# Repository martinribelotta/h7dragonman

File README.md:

# H7-DragonMAN board

STM32H7 LQFP100 board for protocol bridge and industrial control.

## Characterstics:

 - Isolated (see `isolated` branch) and non isolated version
 - STM32H750/743VxTx400MHz in 100LQFP with 8MHz/32.768Khz crystals and ROM Bootloader via USB
 - STM32-based DAP programmer and virtual usb with ROM bootloader via USB
 - External 2/4/8/16MB QSPI flash
 - MicroSD card 1bit slot
 - Two usb otg (FS and HS)
 - 10/100Mb ETH via KSZ8081 in RMII mode
 - RS485 isolated or non-isolated
 - CANBUS isolated or non-isolated
 - Isolated 3.3 to 5V step-up for CANBUS/RS-485 tranceivers
 - One user button
 - One user led
 - 5-24V input via AP63203 DC-DC regulator

## Schematic

## Board dimentions

## 3D preview

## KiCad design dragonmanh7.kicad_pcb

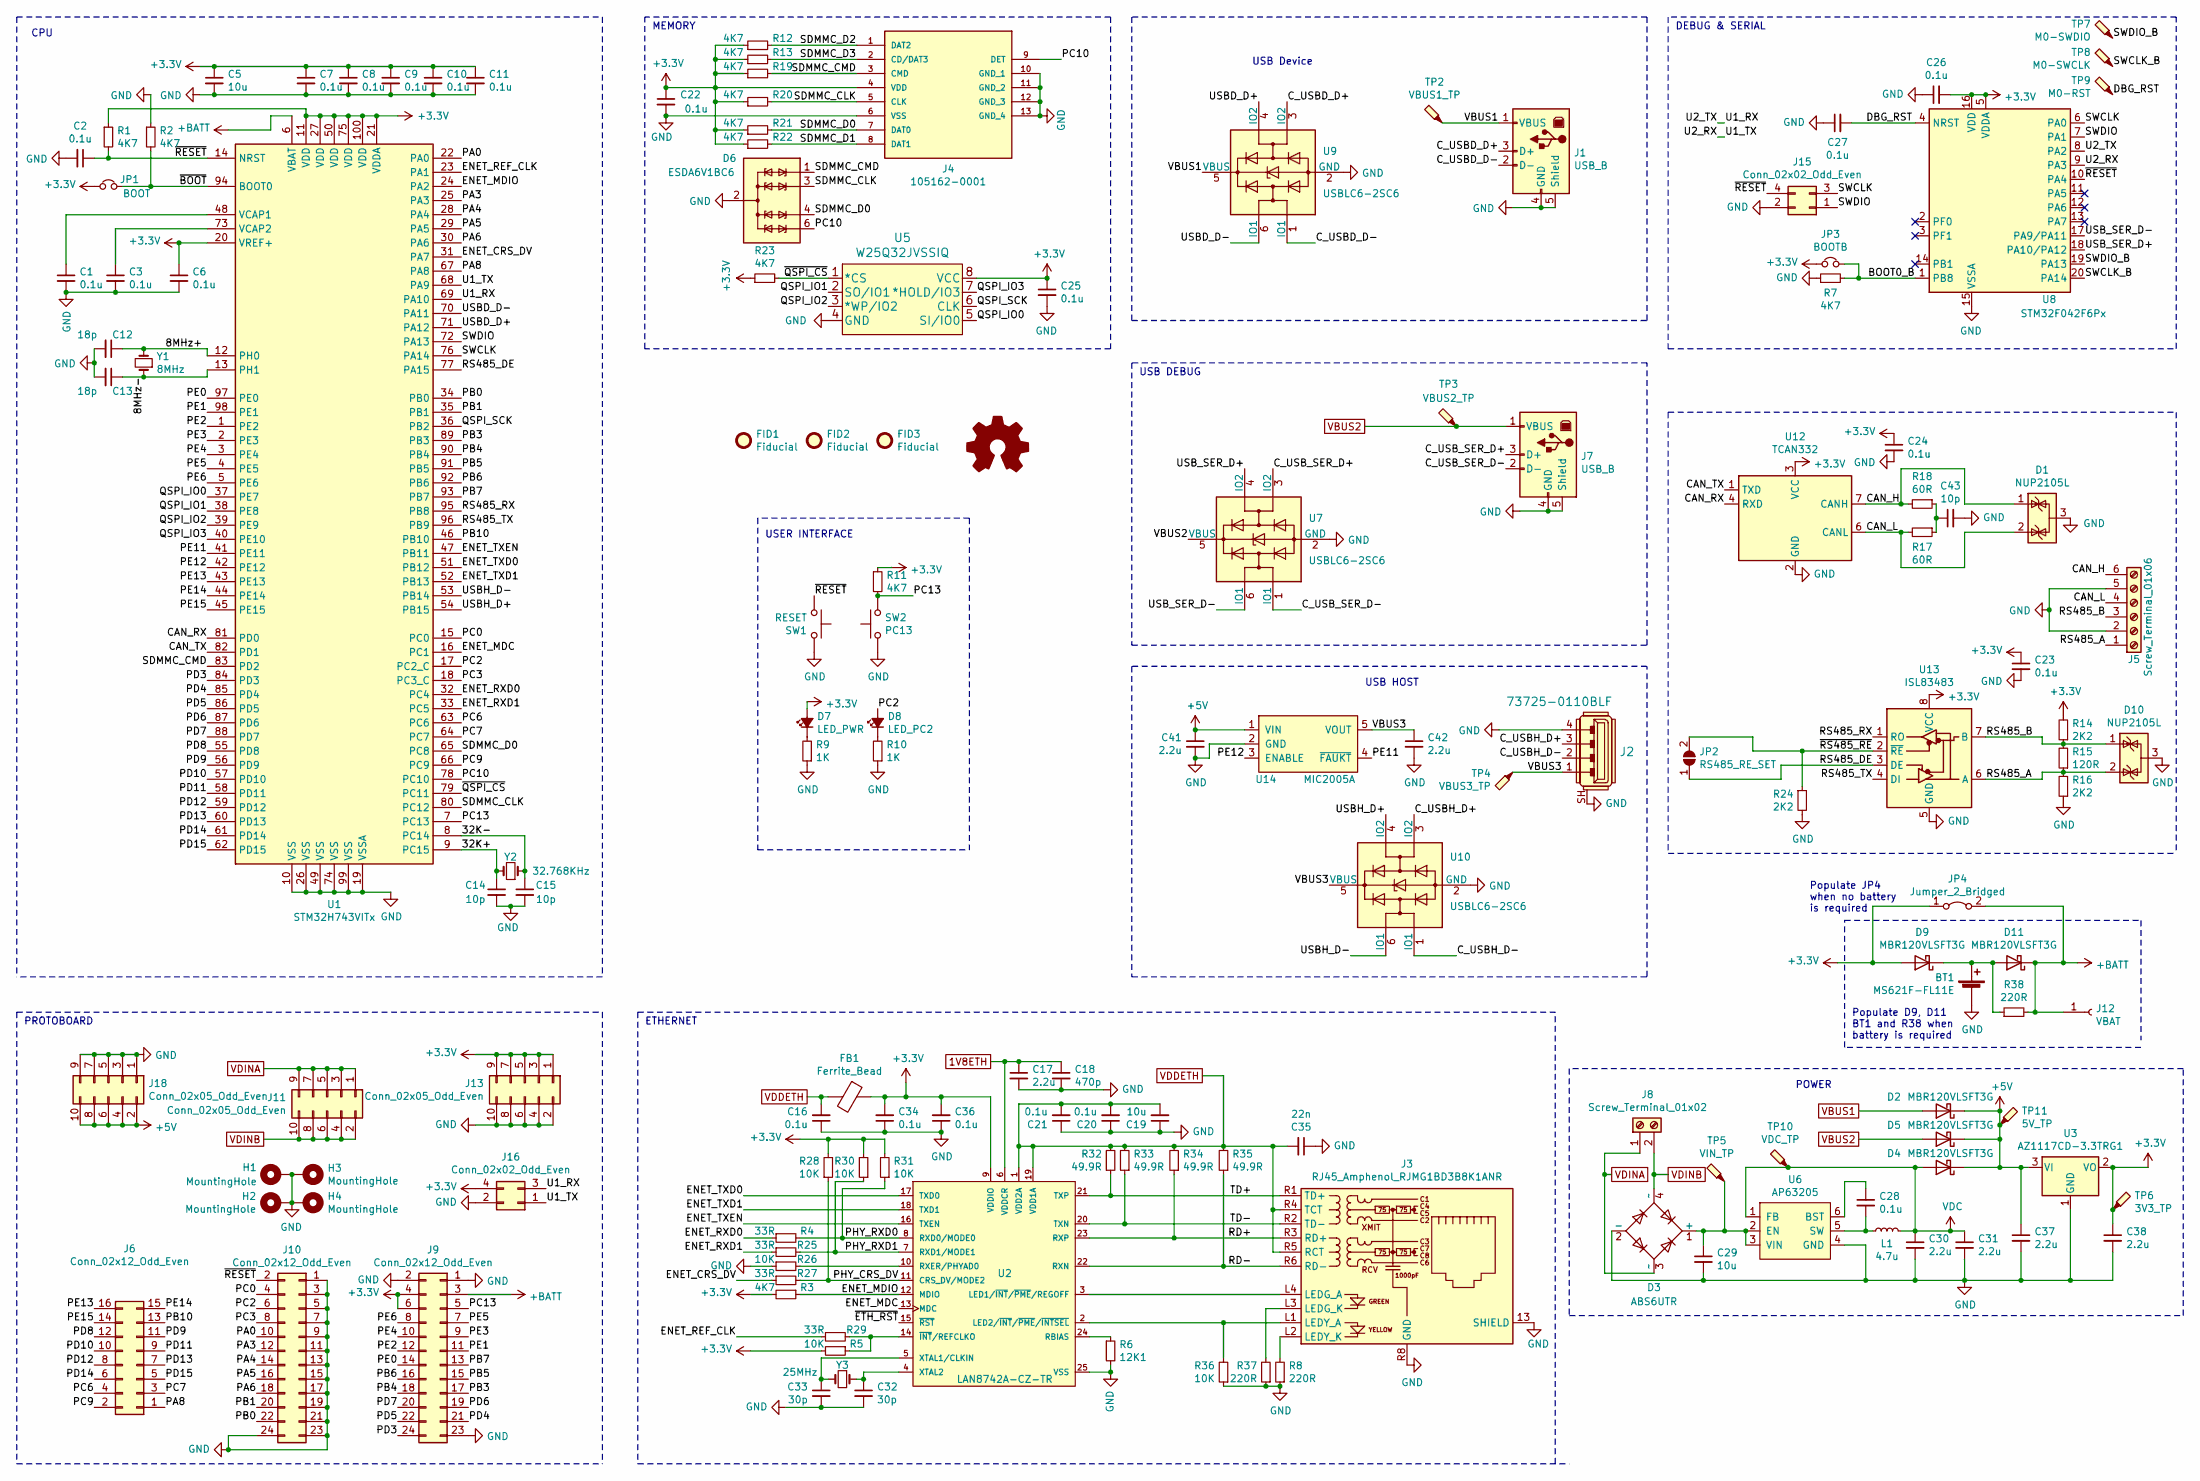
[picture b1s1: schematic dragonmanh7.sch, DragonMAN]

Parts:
BT1: MS621F-FL11E; BatteryHolder_Seiko_MS621F
C1, C2, C3, C6, C7, C8, C9, C10, C11, C16, C20, C21, C22, C23, C24, C25, C26, C27, C28, C34, C36: 0.1u; C_0603_1608Metric
C5, C19, C29: 10u; C_0805_2012Metric
C12, C13: 18p; C_0603_1608Metric
C14, C15, C43: 10p; C_0603_1608Metric
C17, C30, C31, C37, C38, C41, C42: 2.2u; C_0805_2012Metric
C18: 470p; C_0603_1608Metric
C32, C33: 30p; C_0603_1608Metric
C35: 22n; C_0603_1608Metric
D1, D10: NUP2105L; SOT-23
D2, D4, D5, D9, D11: MBR120VLSFT3G; D_SOD-123F
D3: ABS6UTR; Diode_Bridge_Diotec_ABS
D6: ESDA6V1BC6; SOT-23-6
D7: LED_PWR; LED_0805_2012Metric_Castellated
D8: LED_PC2; LED_0805_2012Metric_Castellated
FB1: Ferrite_Bead; L_0603_1608Metric
FID1, FID2, FID3: Fiducial; Fiducial_1mm_Mask2mm
H1, H2, H3, H4: MountingHole; MountingHole_3.2mm_M3_Pad_Via
J1, J7: USB_B; USB_B_Lumberg_2411_02_Horizontal
J2: 73725-0110BLF; USB_A_Female_Vertical_RA_73725-0110BLF; MPN 73725-0110BLF; Digi-Key_PN 609-1041-ND
J3: RJ45_Amphenol_RJMG1BD3B8K1ANR
J4: 105162-0001; MANUFACTURER_PART_NUMBER 105162-0001; MOUSER_PART_NUMBER 538-105162-0001
J5: Screw_Terminal_01x06; PhoenixContact_MC-G_06x5.08mm_Angled
J6: Conn_02x12_Odd_Even; PinSocket_2x08_P2.54mm_Vertical
J8: Screw_Terminal_01x02; PhoenixContact_MC-G_02x5.08mm_Angled
J9, J10: Conn_02x12_Odd_Even; PinSocket_2x12_P2.54mm_Vertical
J11, J13, J18: Conn_02x05_Odd_Even; PinSocket_2x05_P2.54mm_Vertical
J12: VBAT; TestPoint_Loop_D1.80mm_Drill1.0mm_Beaded
J15: Conn_02x02_Odd_Even; Pin_Header_Straight_2x02_Pitch2.54mm
J16: Conn_02x02_Odd_Even; PinSocket_2x02_P2.54mm_Vertical
JP1: BOOT; PinHeader_1x02_P2.54mm_Horizontal
JP2: RS485_RE_SET; SolderJumper-2_P1.3mm_Open_RoundedPad1.0x1.5mm
JP3: BOOTB; PinHeader_1x02_P2.54mm_Vertical
JP4: Jumper_2_Bridged; SolderJumper-2_P1.3mm_Open_RoundedPad1.0x1.5mm
L1: 4.7u; L_6.3x6.3_H3
LOGO1: Logo_Open_Hardware_Small; KiCad-Logo2_8mm_SilkScreen
R1, R2, R3, R7, R11, R12, R13, R19, R20, R21, R22, R23: 4K7; R_0603_1608Metric
R4, R25, R27, R29: 33R; R_0603_1608Metric
R5, R26, R28, R30, R31, R36: 10K; R_0603_1608Metric
R6: 12K1; R_0603_1608Metric
R8, R37, R38: 220R; R_0603_1608Metric
R9, R10: 1K; R_0603_1608Metric
R14, R16, R24: 2K2; R_0603_1608Metric
R15: 120R; R_0603_1608Metric
R17, R18: 60R; R_0603_1608Metric
R32, R33, R34, R35: 49.9R; R_0603_1608Metric
SW1: RESET; SW_Tactile_SPST_Angled_PTS645Vx31-2LFS
SW2: PC13; SW_Tactile_SPST_Angled_PTS645Vx31-2LFS
TP2: VBUS1_TP; TestPoint_Pad_D2.5mm
TP3: VBUS2_TP; TestPoint_Pad_D2.5mm
TP4: VBUS3_TP; TestPoint_Pad_D2.5mm
TP5: VIN_TP; TestPoint_Pad_D2.5mm
TP6: 3V3_TP; TestPoint_Pad_D2.5mm
TP7: M0-SWDIO; TestPoint_Pad_1.0x1.0mm
TP8: M0-SWCLK; TestPoint_Pad_1.0x1.0mm
TP9: M0-RST; TestPoint_Pad_1.0x1.0mm
TP10: VDC_TP; TestPoint_Pad_D2.5mm
TP11: 5V_TP; TestPoint_Pad_D2.5mm
U1: STM32H743VITx; LQFP-100_14x14mm_P0.5mm
U2: LAN8742A-CZ-TR; Microchip-C04-143B-S4QFN-0-0-IPC_C; mouser part number 579-LAN8742A-CZ-TR; digikey description IC TRANSCEIVER 1/1 24SQFN
U3: AZ1117CD-3.3TRG1; TO-252-2
U5: W25Q32JVSSIQ; S25FL127SABMFI101
U6: AP63205; TSOT-23-6
U7, U9, U10: USBLC6-2SC6; SOT-23-6
U8: STM32F042F6Px; TSSOP-20_4.4x6.5mm_P0.65mm
U12: TCAN332; SOT-23-8
U13: ISL83483; SOIC-8_3.9x4.9mm_P1.27mm
U14: MIC2005A; SOT-23-5
Y1: 8MHz; Crystal_SMD_5032-2Pin_5.0x3.2mm
Y2: 32.768KHz; Crystal_SMD_MicroCrystal_CC7V-T1A-2Pin_3.2x1.5mm
Y3: 25MHz; Crystal_SMD_5032-2Pin_5.0x3.2mm

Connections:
1V8ETH: C17.1, C18.1, U2.6 (VDDCR)
+3V3: C5.1, C6.1, C7.1, C8.1, C9.1, C10.1, C11.1, C22.1, C23.1, C24.1, C25.1, C26.2, C34.2, C36.2, C38.1, D7.2 (A), D9.2 (A), FB1.1, J4.4 (VDD), J9.4, J9.6, J13.1, J13.3, J13.5, J13.7, J13.9, J16.4, JP1.1, JP3.1, JP4.1 (A), R1.1, R3.2, R5.2, R11.1, R12.1, R13.1, R14.2, R19.1, R20.1, R21.1, R22.1, R23.1, R28.2, R30.2, R31.2, TP6.1, U1.11 (VDD), U1.20 (VREF+), U1.21 (VDDA), U1.27 (VDD), U1.50 (VDD), U1.75 (VDD), U1.100 (VDD), U2.9 (VDDIO), U3.2 (VO), U5.8 (VCC), U8.5 (VDDA), U8.16 (VDD), U12.3 (VCC), U13.8 (VCC)
+5V: C37.1, C41.1, D2.1 (K), D4.1 (K), D5.1 (K), J18.2, J18.4, J18.6, J18.8, J18.10, TP11.1, U3.3 (VI), U14.1 (VIN)
+BATT: D11.1 (K), J9.3, J12.1, JP4.2 (B), R38.2, U1.6 (VBAT)
/8MHz+: C12.1, U1.12 (PH0), Y1.2
/8MHz-: C13.1, U1.13 (PH1), Y1.1
/32K+: C14.1, U1.9 (PC15), Y2.2
/32K-: C15.1, U1.8 (PC14), Y2.1
/BOOT0_B: JP3.2, R7.2, U8.1 (PB8)
/CAN_H: D1.1 (K), J5.6, R18.2, U12.7 (CANH)
/CAN_L: D1.2 (K), J5.4, R17.2, U12.6 (CANL)
/CAN_RX: U1.81 (PD0), U12.4 (RXD)
/CAN_TX: U1.82 (PD1), U12.1 (TXD)
/C_USBD_D+: J1.3 (D+), U9.3 (IO2)
/C_USBD_D-: J1.2 (D-), U9.1 (IO1)
/C_USBH_D+: J2.3, U10.3 (IO2)
/C_USBH_D-: J2.2, U10.1 (IO1)
/C_USB_SER_D+: J7.3 (D+), U7.3 (IO2)
/C_USB_SER_D-: J7.2 (D-), U7.1 (IO1)
/DBG_RST: C27.2, TP9.1, U8.4 (NRST)
/ENET_CRS_DV: R27.1, U1.31 (PA7)
/ENET_MDC: U1.16 (PC1), U2.13 (MDC)
/ENET_MDIO: R3.1, U1.24 (PA2), U2.12 (MDIO)
/ENET_REF_CLK: R29.1, U1.23 (PA1)
/ENET_RXD0: R4.1, U1.32 (PC4)
/ENET_RXD1: R25.1, U1.33 (PC5)
/ENET_TXD0: U1.51 (PB12), U2.17 (TXD0)
/ENET_TXD1: U1.52 (PB13), U2.18 (TXD1)
/ENET_TXEN: U1.47 (PB11), U2.16 (TXEN)
/PA0: J10.10, U1.22 (PA0)
/PA3: J10.12, U1.25 (PA3)
/PA4: J10.14, U1.28 (PA4)
/PA5: J10.16, U1.29 (PA5)
/PA6: J10.18, U1.30 (PA6)
/PA8: J6.1, U1.67 (PA8)
/PB0: J10.22, U1.34 (PB0)
/PB1: J10.20, U1.35 (PB1)
/PB3: J9.17, U1.89 (PB3)
/PB4: J9.18, U1.90 (PB4)
/PB5: J9.15, U1.91 (PB5)
/PB6: J9.16, U1.92 (PB6)
/PB7: J9.13, U1.93 (PB7)
/PB10: J6.13, U1.46 (PB10)
/PC0: J10.4, U1.15 (PC0)
/PC2: D8.2 (A), J10.6, U1.17 (PC2_C)
/PC3: J10.8, U1.18 (PC3_C)
/PC6: J6.4, U1.63 (PC6)
/PC7: J6.3, U1.64 (PC7)
/PC9: J6.2, U1.66 (PC9)
/PC10: D6.6 (TVS4), J4.9 (DET), U1.78 (PC10)
/PC13: J9.5, R11.2, SW2.2, U1.7 (PC13)
/PD3: J9.24, U1.84 (PD3)
/PD4: J9.21, U1.85 (PD4)
/PD5: J9.22, U1.86 (PD5)
/PD6: J9.19, U1.87 (PD6)
/PD7: J9.20, U1.88 (PD7)
/PD8: J6.12, U1.55 (PD8)
/PD9: J6.11, U1.56 (PD9)
/PD10: J6.10, U1.57 (PD10)
/PD11: J6.9, U1.58 (PD11)
/PD12: J6.8, U1.59 (PD12)
/PD13: J6.7, U1.60 (PD13)
/PD14: J6.6, U1.61 (PD14)
/PD15: J6.5, U1.62 (PD15)
/PE0: J9.14, U1.97 (PE0)
/PE1: J9.11, U1.98 (PE1)
/PE2: J9.12, U1.1 (PE2)
/PE3: J9.9, U1.2 (PE3)
/PE4: J9.10, U1.3 (PE4)
/PE5: J9.7, U1.4 (PE5)
/PE6: J9.8, U1.5 (PE6)
/PE11: U1.41 (PE11), U14.4 (~FAUKT)
/PE12: U1.42 (PE12), U14.3 (ENABLE)
/PE13: J6.16, U1.43 (PE13)
/PE14: J6.15, U1.44 (PE14)
/PE15: J6.14, U1.45 (PE15)
/PHY_CRS_DV: R27.2, R28.1, U2.11 (CRS_DV/MODE2)
/PHY_RXD0: R4.2, R31.1, U2.8 (RXD0/MODE0)
/PHY_RXD1: R25.2, R30.1, U2.7 (RXD1/MODE1)
/QSPI_IO0: U1.37 (PE7), U5.5 (SI/IO0)
/QSPI_IO1: U1.38 (PE8), U5.2 (SO/IO1)
/QSPI_IO2: U1.39 (PE9), U5.3 (*WP/IO2)
/QSPI_IO3: U1.40 (PE10), U5.7 (*HOLD/IO3)
/QSPI_SCK: U1.36 (PB2), U5.6 (CLK)
/RD+: J3.R3 (RD+), R34.1, U2.23 (RXP)
/RD-: J3.R6 (RD-), R35.1, U2.22 (RXN)
/RS485_A: D10.2 (K), J5.1, R15.1, R16.2, U13.6 (A)
/RS485_B: D10.1 (K), J5.3, R14.1, R15.2, U13.7 (B)
/RS485_DE: JP2.1 (A), U1.77 (PA15), U13.3 (DE)
/RS485_RX: U1.95 (PB8), U13.1 (RO)
/RS485_TX: U1.96 (PB9), U13.4 (DI)
/SDMMC_CLK: D6.3 (TVS2), J4.5 (CLK), R20.2, U1.80 (PC12)
/SDMMC_CMD: D6.1 (TVS1), J4.3 (CMD), R19.2, U1.83 (PD2)
/SDMMC_D0: D6.4 (TVS3), J4.7 (DAT0), R21.2, U1.65 (PC8)
/SDMMC_D1: J4.8 (DAT1), R22.2
/SDMMC_D2: J4.1 (DAT2), R12.2
/SDMMC_D3: J4.2 (CD/DAT3), R13.2
/SWCLK: J15.3, U1.76 (PA14), U8.6 (PA0)
/SWCLK_B: TP8.1, U8.20 (PA14)
/SWDIO: J15.1, U1.72 (PA13), U8.7 (PA1)
/SWDIO_B: TP7.1, U8.19 (PA13)
/TD+: J3.R1 (TD+), R32.1, U2.21 (TXP)
/TD-: J3.R2 (TD-), R33.1, U2.20 (TXN)
/U1_RX: J16.3, U1.69 (PA10), U8.8 (PA2)
/U1_TX: J16.1, U1.68 (PA9), U8.9 (PA3)
/USBD_D+: U1.71 (PA12), U9.4 (IO2)
/USBD_D-: U1.70 (PA11), U9.6 (IO1)
/USBH_D+: U1.54 (PB15), U10.4 (IO2)
/USBH_D-: U1.53 (PB14), U10.6 (IO1)
/USB_SER_D+: U7.4 (IO2), U8.18 (PA10/PA12)
/USB_SER_D-: U7.6 (IO1), U8.17 (PA9/PA11)
/VBUS3: C42.1, J2.1, TP4.1, U10.5 (VBUS), U14.5 (VOUT)
/~BOOT: JP1.2, R2.2, U1.94 (BOOT0)
/~QSPI_CS: R23.2, U1.79 (PC11), U5.1 (*CS)
/~RESET: C2.1, J10.2, J15.4, R1.2, SW1.1, U1.14 (NRST), U8.10 (PA4)
/~RS485_RE: JP2.2 (B), R24.1, U13.2 (~RE)
GND: BT1.2 (-), C1.2, C2.2, C3.2, C5.2, C6.2, C7.2, C8.2, C9.2, C10.2, C11.2, C12.2, C13.2, C14.2, C15.2, C16.1, C17.2, C18.2, C19.1, C20.1, C21.1, C22.2, C23.2, C24.2, C25.2, C26.1, C27.1, C29.2, C30.2, C31.2, C32.2, C33.2, C34.1, C35.1, C36.1, C37.2, C38.2, C41.2, C42.2, C43.2, D1.3 (A), D3.2 (-), D6.2 (COM), D6.5 (COM), D10.3 (A), H1.1, H2.1, H3.1, H4.1, J1.4 (GND), J1.5 (Shield), J2.4, J2.SH, J3.13 (SHIELD), J3.R8 (GND), J4.6 (VSS), J4.10 (GND_1), J4.11 (GND_2), J4.12 (GND_3), J4.13 (GND_4), J5.2, J5.5, J7.4 (GND), J7.5 (Shield), J9.1, J9.2, J9.23, J10.1, J10.3, J10.5, J10.7, J10.9, J10.11, J10.13, J10.15, J10.17, J10.19, J10.21, J10.23, J10.24, J13.2, J13.4, J13.6, J13.8, J13.10, J15.2, J16.2, J18.1, J18.3, J18.5, J18.7, J18.9, R2.1, R6.2, R7.1, R8.1, R9.1, R10.1, R16.1, R24.2, R26.1, R36.1, R37.1, SW1.2, SW2.1, U1.10 (VSS), U1.19 (VSSA), U1.26 (VSS), U1.49 (VSS), U1.74 (VSS), U1.99 (VSS), U2.25 (VSS), U3.1 (GND), U5.4 (GND), U6.4 (GND), U7.2 (GND), U8.15 (VSSA), U9.2 (GND), U10.2 (GND), U12.2 (GND), U13.5 (GND), U14.2 (GND)
unnamed: BT1.1 (+), D9.1 (K), D11.2 (A), R38.1
unnamed: C1.1, U1.48 (VCAP1)
unnamed: C3.1, U1.73 (VCAP2)
unnamed: C28.1, U6.6 (BST)
unnamed: C28.2, L1.1, U6.5 (SW)
unnamed: C29.1, D3.1 (+), TP5.1, U6.2 (EN), U6.3 (VIN)
unnamed: C32.1, U2.4 (XTAL2), Y3.1
unnamed: C33.1, U2.5 (XTAL1/CLKIN), Y3.2
unnamed: C43.1, R17.1, R18.1
unnamed: D7.1 (K), R9.2
unnamed: D8.1 (K), R10.2
unnamed: J3.L1 (LEDY_A), R36.2, U2.2 (LED2/~INT~/~PME~/~INTSEL~)
unnamed: J3.L2 (LEDY_K), R8.2
unnamed: J3.L3 (LEDG_K), R37.2
unnamed: J3.L4 (LEDG_A), U2.3 (LED1/~INT~/~PME~/REGOFF)
unnamed: R6.1, U2.24 (RBIAS)
unnamed: R26.2, U2.10 (RXER/PHYAD0)
unnamed: R5.1, R29.2, U2.14 (~INT~/REFCLKO)
VBUS1: D2.2 (A), J1.1 (VBUS), TP2.1, U9.5 (VBUS)
VBUS2: D5.2 (A), J7.1 (VBUS), TP3.1, U7.5 (VBUS)
VDC: C30.1, C31.1, D4.2 (A), L1.2, TP10.1, U6.1 (FB)
VDDETH: C16.2, C19.2, C20.2, C21.2, C35.2, FB1.2, J3.R4 (TCT), J3.R5 (RCT), R32.2, R33.2, R34.2, R35.2, U2.1 (VDD2A), U2.19 (VDD1A)
VDINA: D3.3 (~~), J8.1, J11.1, J11.3, J11.5, J11.7, J11.9
VDINB: D3.4 (~~), J8.2, J11.2, J11.4, J11.6, J11.8, J11.10

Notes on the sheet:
CPU
MEMORY
USER INTERFACE
PROTOBOARD
POWER
DEBUG & SERIAL
ETHERNET
USB Device
USB DEBUG
USB HOST
Populate JP4 when no battery is required
Populate D9, D11 BT1 and R38 when battery is required

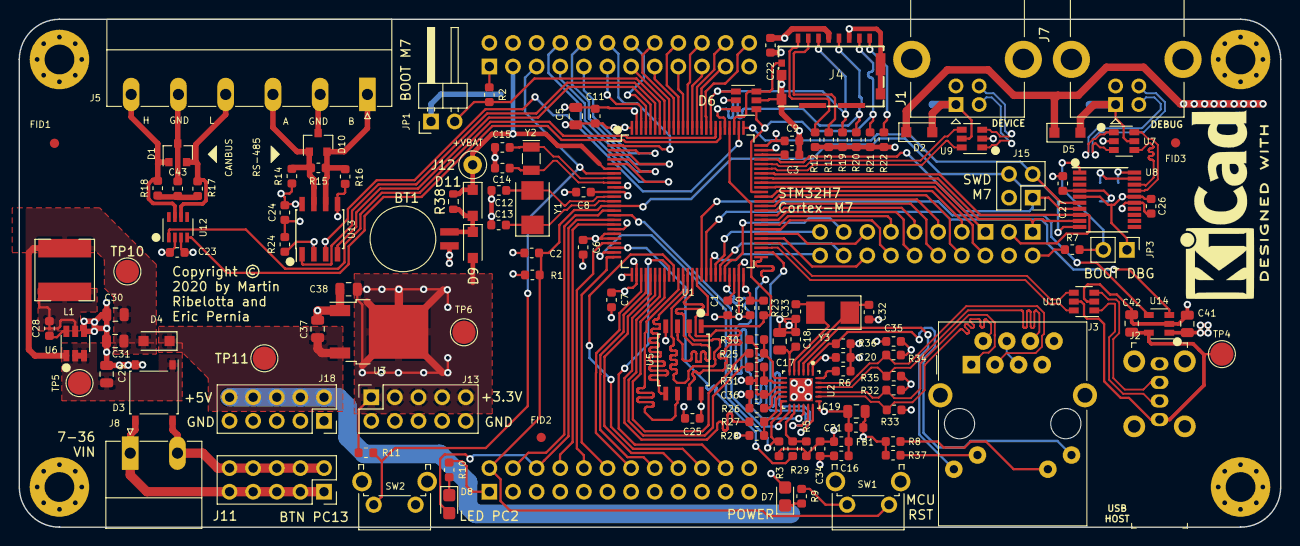
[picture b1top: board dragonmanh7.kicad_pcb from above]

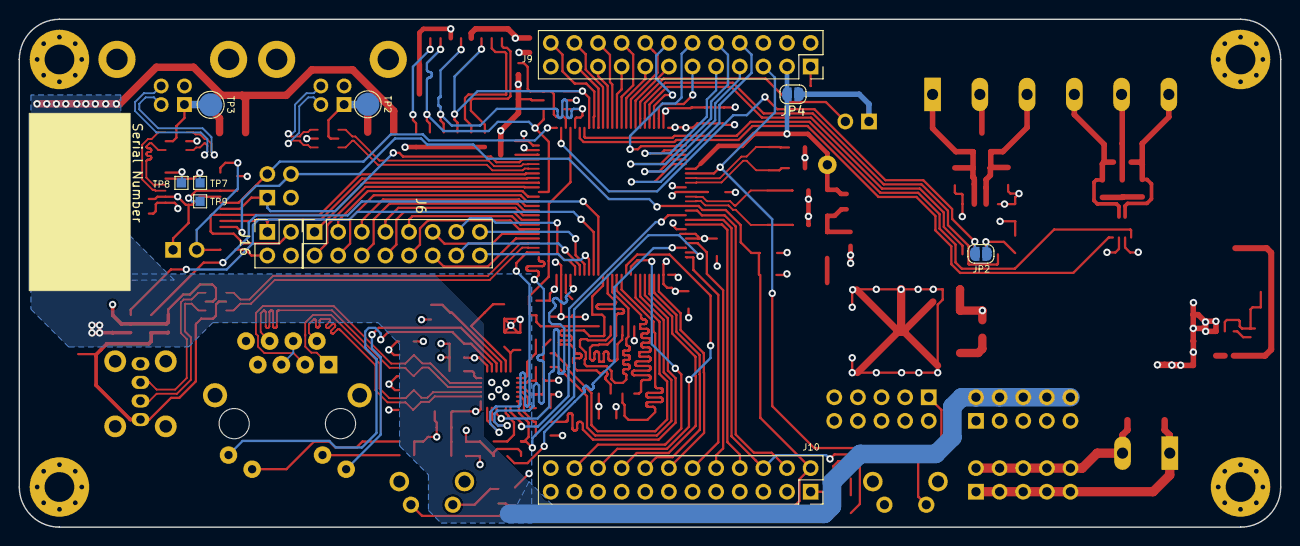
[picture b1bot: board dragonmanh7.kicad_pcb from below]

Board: 4 copper layers, 135.6 x 54.6 mm, 147 parts (11 on the bottom side), 141 nets.

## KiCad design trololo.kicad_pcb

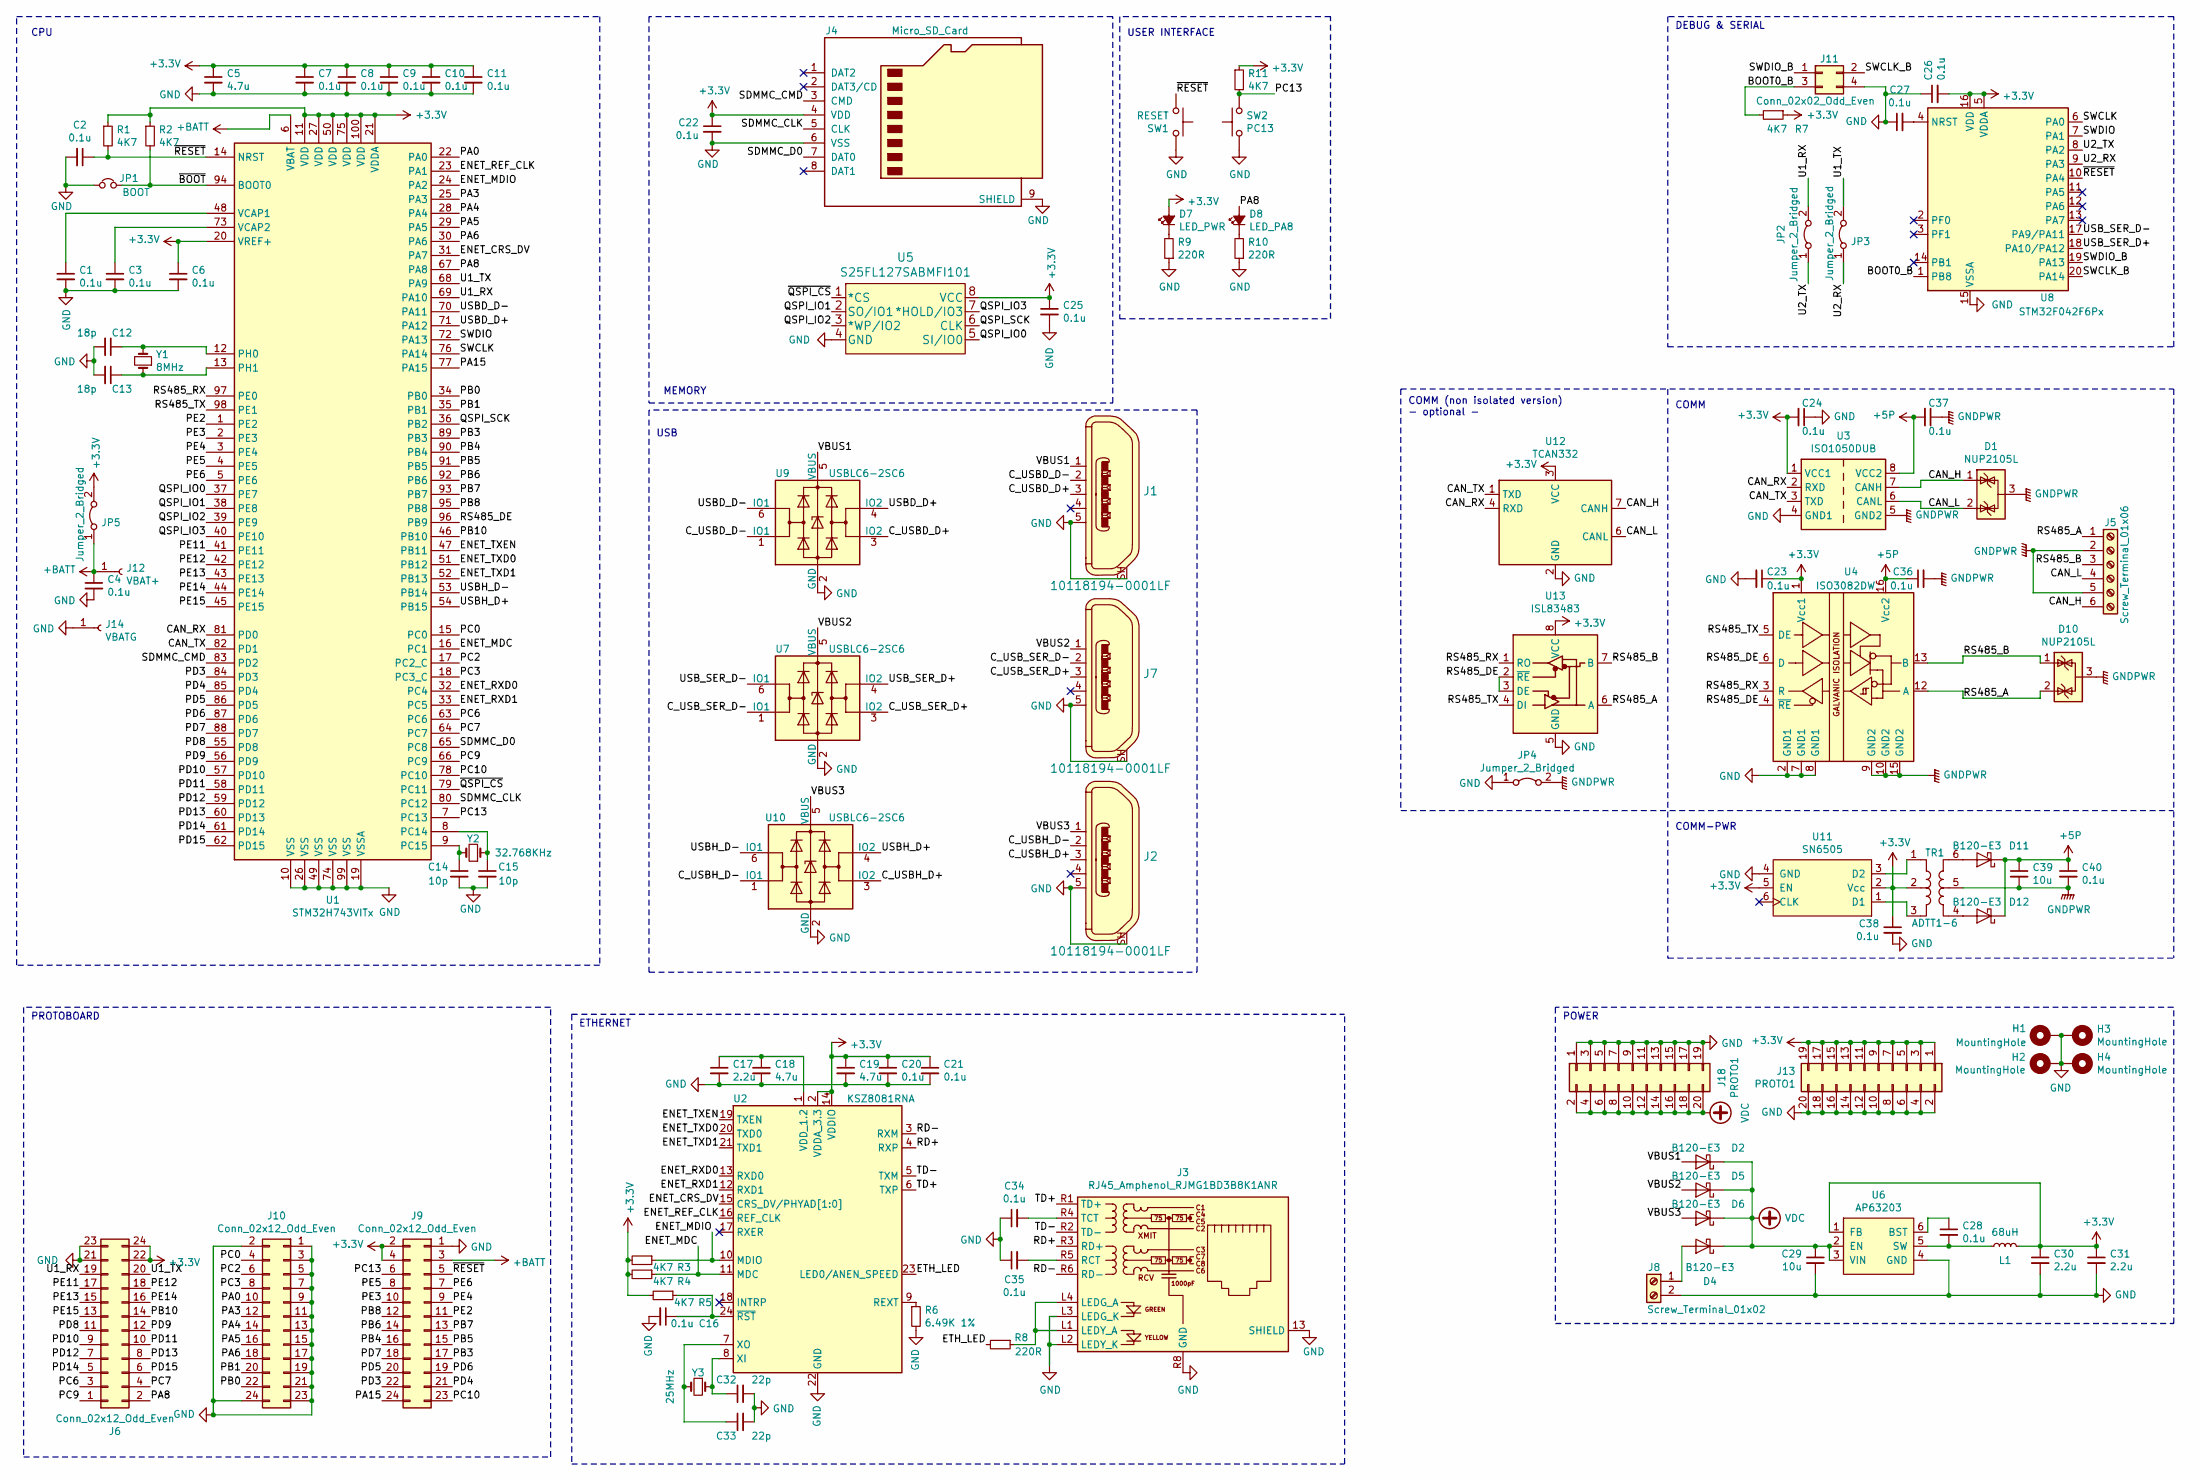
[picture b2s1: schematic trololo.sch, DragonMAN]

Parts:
C1, C2, C3, C4, C6, C7, C8, C9, C10, C11, C16, C20, C21, C22, C23, C24, C25, C26, C27, C28, C34, C35, C36, C37, C38, C40: 0.1u; C_0805_2012Metric
C5, C18, C19: 4.7u; C_0805_2012Metric
C12, C13: 18p; C_0805_2012Metric
C14, C15: 10p; C_0805_2012Metric
C17, C30, C31: 2.2u; C_0805_2012Metric
C29, C39: 10u; C_0805_2012Metric
C32, C33: 22p; C_0805_2012Metric
D1, D10: NUP2105L; SOT-23
D2, D4, D5, D6, D11, D12: B120-E3; D_SMA
D7: LED_PWR; LED_0805_2012Metric_Castellated
D8: LED_PA8; LED_0805_2012Metric_Castellated
H1, H2, H3, H4: MountingHole; MountingHole_3.2mm_M3_Pad_Via
J1, J2, J7: 10118194-0001LF; USB_Micro_B_Female_10118194-0001LF; MPN 10118194-0001LF; Digi-Key_PN 609-4618-1-ND
J3: RJ45_Amphenol_RJMG1BD3B8K1ANR
J4: Micro_SD_Card; microSD_HC_Hirose_DM3D-SF
J5: Screw_Terminal_01x06; PhoenixContact_MC_1,5_6-GF-3.5_1x06_P3.50mm_Horizontal_Thre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
J6, J9, J10: Conn_02x12_Odd_Even; PinSocket_2x12_P2.54mm_Vertical
J8: Screw_Terminal_01x02; PhoenixContact_MC_1,5_2-GF-3.5_1x02_P3.50mm_Horizontal_Thre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
J11: Conn_02x02_Odd_Even; PinHeader_2x02_P2.54mm_Vertical
J12: VBAT+; TestPoint_Loop_D1.80mm_Drill1.0mm_Beaded
J13, J18: PROTO1; PinHeader_2x10_P2.54mm_Vertical
J14: VBATG; TestPoint_Loop_D1.80mm_Drill1.0mm_Beaded
JP1: BOOT; PinHeader_1x02_P2.54mm_Horizontal
JP2, JP3, JP5: Jumper_2_Bridged; SolderJumper-2_P1.3mm_Bridged_RoundedPad1.0x1.5mm
JP4: Jumper_2_Bridged; SolderJumper-2_P1.3mm_Open_RoundedPad1.0x1.5mm
L1: 68uH; L_6.3x6.3_H3
R1, R2, R3, R4, R5, R7, R11: 4K7; R_0805_2012Metric
R6: 6.49K 1%; R_0805_2012Metric
R8, R9, R10: 220R; R_0805_2012Metric
SW1: RESET; SW_Tactile_SPST_Angled_PTS645Vx31-2LFS
SW2: PC13; SW_Tactile_SPST_Angled_PTS645Vx31-2LFS
TR1: ADTT1-6; Pulse_P0926NL
U1: STM32H743VITx; LQFP-100_14x14mm_P0.5mm
U2: KSZ8081RNA; QFN-24-1EP_4x4mm_P0.5mm_EP2.6x2.6mm
U3: ISO1050DUB; SOP-8_6.62x9.15mm_P2.54mm
U4: ISO3082DW; SOIC-16W_7.5x10.3mm_P1.27mm
U5: S25FL127SABMFI101
U6: AP63203; TSOT-23-6
U7, U9, U10: USBLC6-2SC6; SOT-23-6
U8: STM32F042F6Px; TSSOP-20_4.4x6.5mm_P0.65mm
U11: SN6505; SOT-23-6
U12: TCAN332; SOT-23-8
U13: ISL83483; SOIC-8_3.9x4.9mm_P1.27mm
Y1: 8MHz; Crystal_SMD_5032-2Pin_5.0x3.2mm
Y2: 32.768KHz; Crystal_SMD_MicroCrystal_CC7V-T1A-2Pin_3.2x1.5mm
Y3: 25MHz; Crystal_SMD_5032-2Pin_5.0x3.2mm

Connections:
+3V3: C5.1, C6.1, C7.1, C8.1, C9.1, C10.1, C11.1, C19.1, C20.1, C21.1, C22.1, C23.1, C24.2, C25.1, C26.2, C30.1, C31.1, C38.1, D7.2 (A), J4.4 (VDD), J6.22, J6.24, J9.2, J9.4, J13.1, J13.3, J13.5, J13.7, J13.9, J13.11, J13.13, J13.15, J13.17, J13.19, JP5.2 (B), L1.2, R1.1, R2.1, R3.2, R4.2, R5.2, R7.1, R11.1, TR1.2, U1.11 (VDD), U1.20 (VREF+), U1.21 (VDDA), U1.27 (VDD), U1.50 (VDD), U1.75 (VDD), U1.100 (VDD), U2.2 (VDDA_3.3), U2.14 (VDDIO), U3.1 (VCC1), U4.1 (Vcc1), U5.8 (VCC), U6.1 (FB), U8.5 (VDDA), U8.16 (VDD), U11.2 (Vcc), U11.5 (EN), U12.3 (VCC), U13.8 (VCC)
+5P: C36.1, C37.2, C39.1, C40.1, D11.1 (K), D12.1 (K), U3.8 (VCC2), U4.16 (Vcc2)
+BATT: C4.1, J9.3, J12.1, JP5.1 (A), U1.6 (VBAT)
/BOOT0_B: J11.3, R7.2, U8.1 (PB8)
/CAN_H: D1.1 (K), J5.6, U3.7 (CANH), U12.7 (CANH)
/CAN_L: D1.2 (K), J5.4, U3.6 (CANL), U12.6 (CANL)
/CAN_RX: U1.81 (PD0), U3.2 (RXD), U12.4 (RXD)
/CAN_TX: U1.82 (PD1), U3.3 (TXD), U12.1 (TXD)
/C_USBD_D+: J1.3, U9.3 (IO2)
/C_USBD_D-: J1.2, U9.1 (IO1)
/C_USBH_D+: J2.3, U10.3 (IO2)
/C_USBH_D-: J2.2, U10.1 (IO1)
/C_USB_SER_D+: J7.3, U7.3 (IO2)
/C_USB_SER_D-: J7.2, U7.1 (IO1)
/ENET_CRS_DV: U1.31 (PA7), U2.15 (CRS_DV/PHYAD[1:0])
/ENET_MDC: R4.1, U1.16 (PC1), U2.11 (MDC)
/ENET_MDIO: R3.1, U1.24 (PA2), U2.10 (MDIO)
/ENET_REF_CLK: U1.23 (PA1), U2.16 (REF_CLK)
/ENET_RXD0: U1.32 (PC4), U2.13 (RXD0)
/ENET_RXD1: U1.33 (PC5), U2.12 (RXD1)
/ENET_TXD0: U1.51 (PB12), U2.20 (TXD0)
/ENET_TXD1: U1.52 (PB13), U2.21 (TXD1)
/ENET_TXEN: U1.47 (PB11), U2.19 (TXEN)
/ETH_LED: R8.2, U2.23 (LED0/ANEN_SPEED)
/PA0: J10.10, U1.22 (PA0)
/PA3: J10.12, U1.25 (PA3)
/PA4: J10.14, U1.28 (PA4)
/PA5: J10.16, U1.29 (PA5)
/PA6: J10.18, U1.30 (PA6)
/PA8: D8.2 (A), J6.2, U1.67 (PA8)
/PA15: J9.24, U1.77 (PA15)
/PB0: J10.22, U1.34 (PB0)
/PB1: J10.20, U1.35 (PB1)
/PB3: J9.17, U1.89 (PB3)
/PB4: J9.16, U1.90 (PB4)
/PB5: J9.15, U1.91 (PB5)
/PB6: J9.14, U1.92 (PB6)
/PB7: J9.13, U1.93 (PB7)
/PB8: J9.12, U1.95 (PB8)
/PB10: J6.14, U1.46 (PB10)
/PC0: J10.4, U1.15 (PC0)
/PC2: J10.6, U1.17 (PC2_C)
/PC3: J10.8, U1.18 (PC3_C)
/PC6: J6.3, U1.63 (PC6)
/PC7: J6.4, U1.64 (PC7)
/PC9: J6.1, U1.66 (PC9)
/PC10: J9.23, U1.78 (PC10)
/PC13: J9.6, R11.2, SW2.2, U1.7 (PC13)
/PD3: J9.22, U1.84 (PD3)
/PD4: J9.21, U1.85 (PD4)
/PD5: J9.20, U1.86 (PD5)
/PD6: J9.19, U1.87 (PD6)
/PD7: J9.18, U1.88 (PD7)
/PD8: J6.11, U1.55 (PD8)
/PD9: J6.12, U1.56 (PD9)
/PD10: J6.9, U1.57 (PD10)
/PD11: J6.10, U1.58 (PD11)
/PD12: J6.7, U1.59 (PD12)
/PD13: J6.8, U1.60 (PD13)
/PD14: J6.5, U1.61 (PD14)
/PD15: J6.6, U1.62 (PD15)
/PE2: J9.11, U1.1 (PE2)
/PE3: J9.10, U1.2 (PE3)
/PE4: J9.9, U1.3 (PE4)
/PE5: J9.8, U1.4 (PE5)
/PE6: J9.7, U1.5 (PE6)
/PE11: J6.17, U1.41 (PE11)
/PE12: J6.18, U1.42 (PE12)
/PE13: J6.15, U1.43 (PE13)
/PE14: J6.16, U1.44 (PE14)
/PE15: J6.13, U1.45 (PE15)
/QSPI_IO0: U1.37 (PE7), U5.5 (SI/IO0)
/QSPI_IO1: U1.38 (PE8), U5.2 (SO/IO1)
/QSPI_IO2: U1.39 (PE9), U5.3 (*WP/IO2)
/QSPI_IO3: U1.40 (PE10), U5.7 (*HOLD/IO3)
/QSPI_SCK: U1.36 (PB2), U5.6 (CLK)
/RD+: J3.R3 (RD+), U2.4 (RXP)
/RD-: J3.R6 (RD-), U2.3 (RXM)
/RS485_A: D10.2 (K), J5.1, U4.12 (A), U13.6 (A)
/RS485_B: D10.1 (K), J5.3, U4.13 (B), U13.7 (B)
/RS485_DE: U1.96 (PB9), U4.4 (~RE), U4.6 (D), U13.2 (~RE), U13.3 (DE)
/RS485_RX: U1.97 (PE0), U4.3 (R), U13.1 (RO)
/RS485_TX: U1.98 (PE1), U4.5 (DE), U13.4 (DI)
/SDMMC_CLK: J4.5 (CLK), U1.80 (PC12)
/SDMMC_CMD: J4.3 (CMD), U1.83 (PD2)
/SDMMC_D0: J4.7 (DAT0), U1.65 (PC8)
/SWCLK: U1.76 (PA14), U8.6 (PA0)
/SWCLK_B: J11.2, U8.20 (PA14)
/SWDIO: U1.72 (PA13), U8.7 (PA1)
/SWDIO_B: J11.1, U8.19 (PA13)
/TD+: J3.R1 (TD+), U2.6 (TXP)
/TD-: J3.R2 (TD-), U2.5 (TXM)
/U1_RX: J6.19, JP2.2 (B), U1.69 (PA10)
/U1_TX: J6.20, JP3.2 (B), U1.68 (PA9)
/U2_RX: JP3.1 (A), U8.9 (PA3)
/U2_TX: JP2.1 (A), U8.8 (PA2)
/USBD_D+: U1.71 (PA12), U9.4 (IO2)
/USBD_D-: U1.70 (PA11), U9.6 (IO1)
/USBH_D+: U1.54 (PB15), U10.4 (IO2)
/USBH_D-: U1.53 (PB14), U10.6 (IO1)
/USB_SER_D+: U7.4 (IO2), U8.18 (PA10/PA12)
/USB_SER_D-: U7.6 (IO1), U8.17 (PA9/PA11)
/VBUS1: D2.2 (A), J1.1, U9.5 (VBUS)
/VBUS2: D5.2 (A), J7.1, U7.5 (VBUS)
/VBUS3: D6.2 (A), J2.1, U10.5 (VBUS)
/~BOOT: JP1.2, R2.2, U1.94 (BOOT0)
/~QSPI_CS: U1.79 (PC11), U5.1 (*CS)
/~RESET: C2.1, J9.5, R1.2, SW1.1, U1.14 (NRST), U8.10 (PA4)
GND: C1.2, C2.2, C3.2, C4.2, C5.2, C6.2, C7.2, C8.2, C9.2, C10.2, C11.2, C12.2, C13.2, C14.2, C15.2, C16.2, C17.2, C18.2, C19.2, C20.2, C21.2, C22.2, C23.2, C24.1, C25.2, C26.1, C27.1, C29.2, C30.2, C31.2, C32.2, C33.2, C34.1, C35.1, C38.2, H1.1, H2.1, H3.1, H4.1, J1.5, J1.SH, J2.5, J2.SH, J3.13 (SHIELD), J3.L2 (LEDY_K), J3.L3 (LEDG_K), J3.R8 (GND), J4.6 (VSS), J4.9 (SHIELD), J6.21, J6.23, J7.5, J7.SH, J8.2, J9.1, J10.1, J10.2, J10.3, J10.5, J10.7, J10.9, J10.11, J10.13, J10.15, J10.17, J10.19, J10.21, J10.23, J10.24, J11.4, J13.2, J13.4, J13.6, J13.8, J13.10, J13.12, J13.14, J13.16, J13.18, J13.20, J14.1, J18.1, J18.3, J18.5, J18.7, J18.9, J18.11, J18.13, J18.15, J18.17, J18.19, JP1.1, JP4.1 (A), R6.2, R9.1, R10.1, SW1.2, SW2.1, U1.10 (VSS), U1.19 (VSSA), U1.26 (VSS), U1.49 (VSS), U1.74 (VSS), U1.99 (VSS), U2.22 (GND), U2.25 (GND), U3.4 (GND1), U4.2 (GND1), U4.7 (GND1), U4.8 (GND1), U5.4 (GND), U6.4 (GND), U7.2 (GND), U8.15 (VSSA), U9.2 (GND), U10.2 (GND), U11.4 (GND), U12.2 (GND), U13.5 (GND)
GNDPWR: C36.2, C37.1, C39.2, C40.2, D1.3 (A), D10.3 (A), J5.2, J5.5, JP4.2 (B), TR1.5, U3.5 (GND2), U4.9 (GND2), U4.10 (GND2), U4.15 (GND2)
unnamed: C1.1, U1.48 (VCAP1)
unnamed: C3.1, U1.73 (VCAP2)
unnamed: C12.1, U1.12 (PH0), Y1.2
unnamed: C13.1, U1.13 (PH1), Y1.1
unnamed: C14.1, U1.9 (PC15), Y2.2
unnamed: C15.1, U1.8 (PC14), Y2.1
unnamed: C16.1, R5.1, U2.24 (~RST)
unnamed: C17.1, C18.1, U2.1 (VDD_1.2)
unnamed: C27.2, U8.4 (NRST)
unnamed: C28.1, U6.6 (BST)
unnamed: C28.2, L1.1, U6.5 (SW)
unnamed: C32.1, U2.8 (XI), Y3.1
unnamed: C33.1, U2.7 (XO), Y3.2
unnamed: C34.2, J3.R4 (TCT)
unnamed: C35.2, J3.R5 (RCT)
unnamed: D4.2 (A), J8.1
unnamed: D7.1 (K), R9.2
unnamed: D8.1 (K), R10.2
unnamed: D11.2 (A), TR1.6
unnamed: D12.2 (A), TR1.4
unnamed: J3.L1 (LEDY_A), J3.L4 (LEDG_A), R8.1
unnamed: R6.1, U2.9 (REXT)
unnamed: TR1.1, U11.3 (D2)
unnamed: TR1.3, U11.1 (D1)
VDC: C29.1, D2.1 (K), D4.1 (K), D5.1 (K), D6.1 (K), J18.2, J18.4, J18.6, J18.8, J18.10, J18.12, J18.14, J18.16, J18.18, J18.20, U6.2 (EN), U6.3 (VIN)

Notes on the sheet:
CPU
MEMORY
USER INTERFACE
PROTOBOARD
POWER
DEBUG & SERIAL
ETHERNET
USB
COMM
COMM-PWR
COMM (non isolated version) - optional -

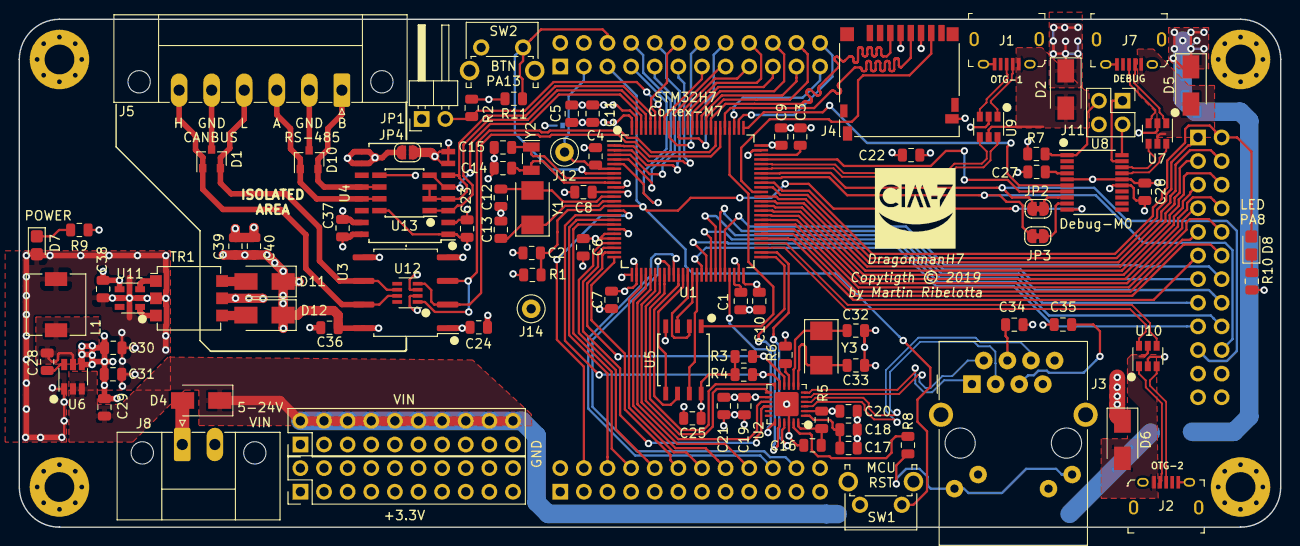
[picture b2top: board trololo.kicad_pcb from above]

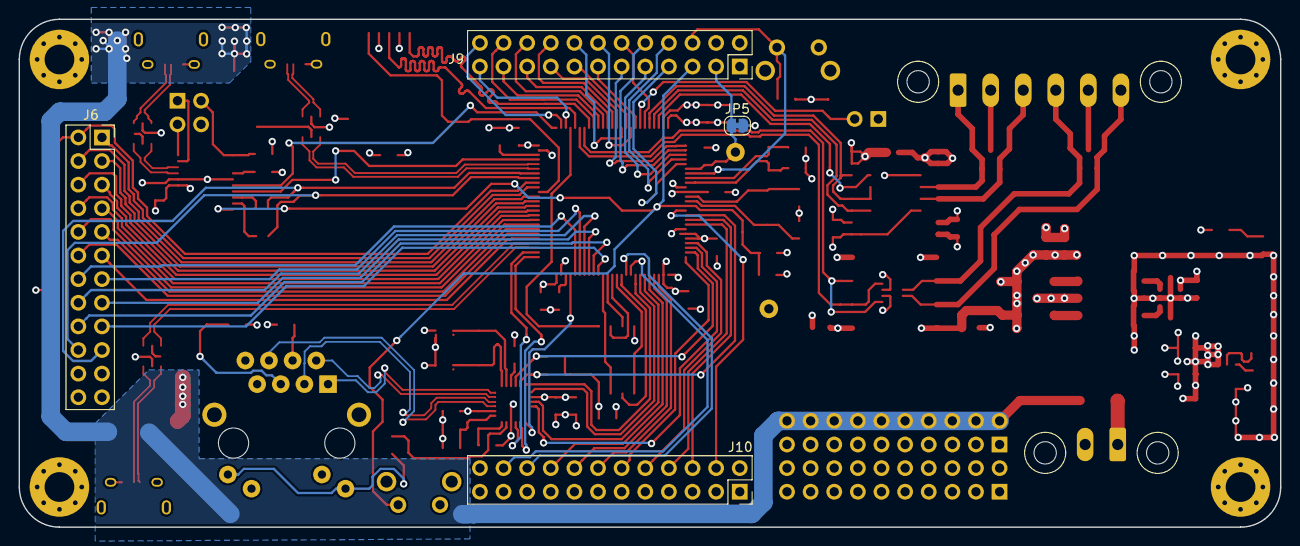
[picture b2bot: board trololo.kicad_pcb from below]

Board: 4 copper layers, 135.6 x 54.6 mm, 105 parts (4 on the bottom side), 135 nets.

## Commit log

2019-02-25 Final aproach with no can/485 isolation
2019-02-26 First isolation aproach
2019-02-26 Add missing files
2019-05-12 Unknown changes
2019-05-18 More unprecie modifications
    The log messages on this git sucks
2019-05-18 Add battery pins
2019-05-19 Add README and docs with 3D images
2019-05-21 Add logos and change reset button and user led position
2019-05-21 Add packages 3d and last minutes touchs
2019-05-21 Add exported gerbers
2019-05-24 Create LICENSE
2019-05-24 Add patrocinator logo, silkscreen correctios and minor route changes
2019-05-24 Rename stupid name of trololo to more super-cool name dragonmanh7
2019-05-24 Minor changes in libs names
2019-05-25 Change power and rs485/can connectors
2019-05-25 Fix power connector Y-position
2019-05-25 Update gerbers
2019-05-26 Fix L1 footprint
2019-05-26 update gerbers for production
2019-05-28 Update images and README
2019-06-06 Minimal changes for production based on prototipe pitfalls
    - Change bootloader jumper polarity
    - More spaces in some capacitores
    - Add SWD-M7 connector in path to debugger mcu
2019-06-06 Remove unnecesary overlaps
2019-06-19 Improve isolated area
2019-06-20 Add usb host power controller
2019-06-28 Change USB connectors to more hardness versions:
    - OTG1 to USB-B
    - DAP to USB-B
    - OTG2 to USB-A horizontal rigth angle
    - Move leds and buttons to bottom side
    - Align up and bottom headers
    - Add HOST power control on OTG2
2019-06-29 Move gpio near gpio button and reubicate power led, update documentation
2019-07-01 Fix gnd plane beside RJ45
2019-07-01 Reroute the power plane above RJ45 to prevent coupling
2019-07-01 Improve ethernet connections (impedance matching TODO)
2019-07-01 Impreove some traces
2019-07-01 Remove rescue library from schematic
2019-07-01 Clear schematic library table and minor pcb footprint capacitor reorganization
2019-07-01 Improve reset tracesu
2019-07-01 Add rs485/CANBUS optional termination footprints
2019-07-01 Minor changes in some traces
2019-07-02 Remove non-isolated version of board
2019-07-07 Backup some minor changes
2019-07-07 Revamp to non-isolated only
2019-08-25 Gerbers and clean information
2019-09-20 NonISO: Pullup in SDIO
2019-09-28 Change led resistor from 220R to 1K
2019-11-22 Tune track length for QSPI, ETH and SDMMC
2019-12-01 Improve RS485 DE/nRE with jumper
2019-12-01 Fix interface schematic align and distriburtion
2019-12-01 Remove old logo and put kicad logo
2019-12-01 Add fidutial for automatic mounting
2019-12-01 Update docs and images
2019-12-08 Improve oscilator ground
2020-01-12 Add voltage testpoints
2020-10-07 Change PHY to LAN8742 and change power scheme to improve 5V handling
2020-11-05 Improve schematic and PCB
2020-11-06 Change uSD card connector by Molex 1051620001
2020-11-06 Change usb-c to old usb-b connectors, move uSD to outter
2020-11-06 Rearrange logos and vias
2020-11-06 Point of save
2020-11-06 Move rigth side expansion to center
2020-11-06 Saved point
2020-11-10 Add ESD filters to uSD connector, improve routing
2020-11-25 Minor changes, add uSD DET on PC10
2020-11-25 ETH and usb skew near of unmatched area
2021-11-01 Point of restoration

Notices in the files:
dragonmanh7.kicad_pcb:
Copyright ©
trololo.kicad_pcb:
Copytigth © 2019
parts and their libraries:
Copyright 2016 Accelerated Designs. All rights reserved.
